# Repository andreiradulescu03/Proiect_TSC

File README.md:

# OpenBook – Proiect TSC 2025

Acest proiect reprezinta un prototip de eBook reader open-source, construit in jurul microcontrolerului ESP32-C6 si echipat cu afisaj E-Ink, baterie Li-Po, incarcare prin USB-C, slot microSD si senzori de mediu. Proiectul a inclus realizarea schemei electrice, a placii PCB, a modelului 3D complet si a fisierelor pentru fabricatie.

---

## Diagrama bloc

```mermaid
flowchart TB
  USB-C -->|5V| CHG["Battery Charger MCP73831"]
  CHG -->|Charging| BAT["LiPo Battery"]
  BAT --> LDO["3.3V LDO Regulator"]
  LDO -->|3.3V| ESP["ESP32-C6"]
  LDO -->|3.3V| EPD["E-Ink Display"]
  LDO -->|3.3V| SD["SD Card"]
  LDO -->|3.3V| BME["Sensor BME688"]
  LDO -->|3.3V| RTC["RTC DS3231"]
  LDO -->|3.3V| MAX["Battery Monitor MAX17048"]
  
  ESP -- SPI --> EPD
  ESP -- SPI --> SD
  ESP -- I2C --> BME
  ESP -- I2C --> RTC
  ESP -- I2C --> MAX
  ESP -- GPIO --> BTN["Buttons (3x)"]
```

---

## Functionalitate hardware

- **ESP32-C6** gestioneaza toate perifericele prin GPIO, SPI si I2C
- **Afisajul E-Ink** este controlat prin SPI si are semnale dedicate pentru RESET, DC si BUSY
- **Bateria Li-Po** este incarcata printr-un controler MCP73831 si monitorizata cu MAX17048
- **Senzorul BME688** masoara temperatura, umiditatea, presiunea si compusii volatili
- **Modulul RTC DS3231** mentine ora exacta si permite deep sleep eficient
- **Cardul microSD** este conectat la aceeasi magistrala SPI
- Toate componentele sunt montate pe layer-ul TOP si rutarea este realizata in 2 straturi

---

## Pinout ESP32-C6

| Componenta         | Pin ESP32-C6 | Interfata |
|--------------------|--------------|-----------|
| E-Ink BUSY         | IO3          | GPIO      |
| E-Ink DC           | IO5          | GPIO      |
| E-Ink RESET        | IO23         | GPIO      |
| E-Ink CS           | IO10         | SPI       |
| E-Ink MOSI         | IO7          | SPI       |
| E-Ink SCK          | IO6          | SPI       |
| SD Card CS         | IO4          | SPI       |
| SD Card MISO       | IO2          | SPI       |
| I2C SDA            | IO18         | I2C       |
| I2C SCL            | IO19         | I2C       |
| Butoane            | GPIO10/11/12 | GPIO      |

---

## Fisiere incluse

- `*.sch`, `*.brd` – schema electrica si design-ul PCB
- `Gerber/` – fisiere de productie
- `3D/` – modelul 3D al PCB-ului cu toate componentele atasate (baterie, ecran, carcasa)
- `BOM.csv` – lista de componente
- `README.md` – acest fisier

---

## Observatii

- Traseele de alimentare au latimea de 0.3mm, restul traseelor 0.15mm
- PCB-ul are grosimea de 1mm si contine planuri de masa pe ambele straturi
- Conectorii, ecranul si bateria au fost integrati in modelul 3D si testati pentru incadrare in carcasa
- Carcasa a fost importata si aliniata cu PCB-ul pentru randare
- Fisierele au fost verificate cu ERC si DRC

---

## Disclaimer subtil

Acest proiect a fost realizat cu atentie la detalii si cu efort considerabil, in contextul unor cerinte tehnice variate si din ce in ce mai ambitioase. Procesul de proiectare in Fusion 360 a oferit ocazii multiple de invatare, unele mai interesante decat altele. Daca anumite alegeri de design par neasteptate, ele reflecta acest parcurs complex.

---

## Bill of Materials

|   Qty | Value                                                                          | Device                                                                         | Package                                                | Parts                                                                                                   | Description                                                                                                                                                                                                                                                                                                                                                                                                                                                                                          |
|------:|:-------------------------------------------------------------------------------|:-------------------------------------------------------------------------------|:-------------------------------------------------------|:--------------------------------------------------------------------------------------------------------|:-----------------------------------------------------------------------------------------------------------------------------------------------------------------------------------------------------------------------------------------------------------------------------------------------------------------------------------------------------------------------------------------------------------------------------------------------------------------------------------------------------|
|     1 |                                                                                | ADAFRUIT_LEDCHIP-LED0603                                                       | ADAFRUIT_CHIP-LED0603                                  | CHG_LED                                                                                                 | LED                                                                                                                                                                                                                                                                                                                                                                                                                                                                                                  |
|     1 |                                                                                | SJ                                                                             | SJ                                                     | SJ1                                                                                                     | SMD solder JUMPER                                                                                                                                                                                                                                                                                                                                                                                                                                                                                    |
|     1 | 0.47                                                                           | ESP32_WROVER_EAGLE-LTSPICE_RR0402                                              | ESP32_WROVER_EAGLE-LTSPICE_R0402                       | R3                                                                                                      | RESISTOR, European symbol                                                                                                                                                                                                                                                                                                                                                                                                                                                                            |
|     1 | 100k                                                                           | ESP32_WROVER_EAGLE-LTSPICE_RR0402                                              | ESP32_WROVER_EAGLE-LTSPICE_R0402                       | R1_PWRUSB                                                                                               | RESISTOR, European symbol                                                                                                                                                                                                                                                                                                                                                                                                                                                                            |
|     7 | 100nF                                                                          | EAGLE-LTSPICE_CC0402                                                           | EAGLE-LTSPICE_C0402                                    | C1, C2, C4_USB, C6, C8, C10, C_DELAY                                                                    | CAPACITOR, European symbol                                                                                                                                                                                                                                                                                                                                                                                                                                                                           |
|     1 | 100uF                                                                          | EAGLE-LTSPICE_CC0402                                                           | EAGLE-LTSPICE_C0402                                    | C9                                                                                                      | CAPACITOR, European symbol                                                                                                                                                                                                                                                                                                                                                                                                                                                                           |
|     1 | 100uF                                                                          | RCL_CPOL-EUCT3528                                                              | RCL_CT3528                                             | C3                                                                                                      | POLARIZED CAPACITOR, European symbol                                                                                                                                                                                                                                                                                                                                                                                                                                                                 |
|    16 | 10k                                                                            | ESP32_WROVER_EAGLE-LTSPICE_RR0402                                              | ESP32_WROVER_EAGLE-LTSPICE_R0402                       | R1, R1_PINH, R1_PINH1, R2_PINH, R2_PINH1, R4, R5, R6, R7, R8, R9, R10, R_BOOT, R_CHANGE, R_CL1, R_RESET | RESISTOR, European symbol                                                                                                                                                                                                                                                                                                                                                                                                                                                                            |
|     1 | 10uF                                                                           | EAGLE-LTSPICE_CC0402                                                           | EAGLE-LTSPICE_C0402                                    | C7                                                                                                      | CAPACITOR, European symbol                                                                                                                                                                                                                                                                                                                                                                                                                                                                           |
|     1 | 112A-TAAR-R03_ATTEND                                                           | 112A-TAAR-R03_ATTEND                                                           | 112ATAARR03ATTEND                                      | J4                                                                                                      | Micro SD Card Socket, Push-Push Type, Top Mount, SMT, H=1.83mm, 10u                                                                                                                                                                                                                                                                                                                                                                                                                                  |
|     1 | 15                                                                             | ESP32_WROVER_EAGLE-LTSPICE_RR0402                                              | ESP32_WROVER_EAGLE-LTSPICE_R0402                       | R_CAPACITOR                                                                                             | RESISTOR, European symbol                                                                                                                                                                                                                                                                                                                                                                                                                                                                            |
|     1 | 1uF                                                                            | EAGLE-LTSPICE_CC0402                                                           | EAGLE-LTSPICE_C0402                                    | C5                                                                                                      | CAPACITOR, European symbol                                                                                                                                                                                                                                                                                                                                                                                                                                                                           |
|    10 | 1uF/50V                                                                        | EAGLE-LTSPICE_CC0402                                                           | EAGLE-LTSPICE_C0402                                    | EPD_C1, EPD_C2, EPD_C5, EPD_C6, EPD_C7, EPD_C8, EPD_C9, EPD_C10, EPD_C11, EPD_C12                       | CAPACITOR, European symbol                                                                                                                                                                                                                                                                                                                                                                                                                                                                           |
|     1 | 2.2                                                                            | ESP32_WROVER_EAGLE-LTSPICE_RR0402                                              | ESP32_WROVER_EAGLE-LTSPICE_R0402                       | R2                                                                                                      | RESISTOR, European symbol                                                                                                                                                                                                                                                                                                                                                                                                                                                                            |
|     1 | 200                                                                            | ESP32_WROVER_EAGLE-LTSPICE_RR0402                                              | ESP32_WROVER_EAGLE-LTSPICE_R0402                       | R1_BAT                                                                                                  | RESISTOR, European symbol                                                                                                                                                                                                                                                                                                                                                                                                                                                                            |
|     2 | 20V/4.2A/52mO/1.4W                                                             | ESP32_WROVER_SPARKFUN-DISCRETESEMI_MOSFET_PCH-DMG2305UX-7                      | ESP32_WROVER_SPARKFUN-DISCRETESEMI_SOT23-3             | Q1, Q2                                                                                                  | P-channel MOSFETs                                                                                                                                                                                                                                                                                                                                                                                                                                                                                    |
|     1 | 2k                                                                             | ESP32_WROVER_EAGLE-LTSPICE_RR0402                                              | ESP32_WROVER_EAGLE-LTSPICE_R0402                       | R2_BAT                                                                                                  | RESISTOR, European symbol                                                                                                                                                                                                                                                                                                                                                                                                                                                                            |
|     5 | 4.7uF                                                                          | EAGLE-LTSPICE_CC0402                                                           | EAGLE-LTSPICE_C0402                                    | C1_BAT, C1_BAT1, C1_BAT2, C2_BAT, C5_USB                                                                | CAPACITOR, European symbol                                                                                                                                                                                                                                                                                                                                                                                                                                                                           |
|     1 | 4.7uF/25V                                                                      | EAGLE-LTSPICE_CC0402                                                           | EAGLE-LTSPICE_C0402                                    | C4                                                                                                      | CAPACITOR, European symbol                                                                                                                                                                                                                                                                                                                                                                                                                                                                           |
|     2 | 5k1                                                                            | ESP32_WROVER_EAGLE-LTSPICE_RR0402                                              | ESP32_WROVER_EAGLE-LTSPICE_R0402                       | R2-USB, R2-USB1                                                                                         | RESISTOR, European symbol                                                                                                                                                                                                                                                                                                                                                                                                                                                                            |
|     1 | 68uH                                                                           | 744043680IND_4828-WE-TPC_WRE                                                   | IND_4828-WE-TPC_WRE                                    | L1                                                                                                      |                                                                                                                                                                                                                                                                                                                                                                                                                                                                                                      |
|     1 | BD5229G-TR                                                                     | BD5229G-TR                                                                     | SOT95P280X125-5N                                       | IC1                                                                                                     | Voltage Detector with Adjustable Delay Time: CMOS processes are utilized to develop high precision, low current consumption CMOS reset ICs that allow arbitrary setting of the delay time. The extensive lineup includes both Nch Open Drain and CMOS output types in a wide range of detection voltages (from 2.3V to 6.0V, in 0.1V steps), enabling selection of the ideal solution based on customer requirements. In addition, the entire series is of course both lead-free and RoHS-compliant. |
|     3 | BUTTON_CUSYOMV1                                                                | BUTTON_CUSYOMV1                                                                | MYBUTTON                                               | BOOT_BUTTON, CHANGE_BUTTON, RESET_BUTTON                                                                |                                                                                                                                                                                                                                                                                                                                                                                                                                                                                                      |
|     1 | CPH3225A                                                                       | CPH3225A                                                                       | CAPCP3225X100N                                         | C10_SUPERCAP                                                                                            | Cap 0.011F 3.3V 1210 Flat Check availability                                                                                                                                                                                                                                                                                                                                                                                                                                                         |
|     1 | DS3231SN#                                                                      | DS3231SN#                                                                      | SOIC127P1032X265-16N                                   | U3                                                                                                      | Real Time Clock Serial 16-Pin SOIC W T/R     Check availability                                                                                                                                                                                                                                                                                                                                                                                                                                      |
|     1 | ESP32-C6-WROOM-1-N8                                                            | ESP32-C6-WROOM-1-N8                                                            | XCVR_ESP32-C6-WROOM-1-N8                               | U2                                                                                                      | Check availability                                                                                                                                                                                                                                                                                                                                                                                                                                                                                   |
|     1 | ESP32C6_VARISTORCN1812                                                         | ESP32C6_VARISTORCN1812                                                         | ESP32C6_VARISTOR_CT/CN1812                             | PFMF.050.1                                                                                              | VARISTOR                                                                                                                                                                                                                                                                                                                                                                                                                                                                                             |
|     2 | ESP32_WROVER_AVX---SD0805S020S1R0_AVX_SD0805S020S1R0_0_0AVX_SD0805S020S1R0_0_0 | ESP32_WROVER_AVX---SD0805S020S1R0_AVX_SD0805S020S1R0_0_0AVX_SD0805S020S1R0_0_0 | ESP32_WROVER_AVX---SD0805S020S1R0_AVX_SD0805S020S1R0_0 | D2, D7                                                                                                  | Schottky Barrier Rectifier Diode                                                                                                                                                                                                                                                                                                                                                                                                                                                                     |
|     1 | ESP32_WROVER_BME680_BME680                                                     | ESP32_WROVER_BME680_BME680                                                     | ESP32_WROVER_BME680_PSON80P300X300X100-8N              | SENSOR2                                                                                                 | Integrated Environmental Unit                                                                                                                                                                                                                                                                                                                                                                                                                                                                        |
|     1 | ESP32_WROVER_SPARKFUN-IC-POWER_MCP73831                                        | ESP32_WROVER_SPARKFUN-IC-POWER_MCP73831                                        | ESP32_WROVER_SPARKFUN-IC-POWER_SOT23-5                 | MCP73831                                                                                                | MCP73831T Li-Ion, Li-Pol Controller                                                                                                                                                                                                                                                                                                                                                                                                                                                                  |
|     1 | FH34SRJ-24S-0.5SH_99_                                                          | FH34SRJ-24S-0.5SH_99_                                                          | FH34SRJ24S05SH99                                       | J1                                                                                                      | (0.50mm) Surface Mount, Right Angle                                                                                                                                                                                                                                                                                                                                                                                                                                                                  |
|     1 | MAX17048G+T10                                                                  | MAX17048G+T10                                                                  | SON50P200X200X80-9N                                    | U4                                                                                                      | Check availability                                                                                                                                                                                                                                                                                                                                                                                                                                                                                   |
|     3 | MBR0530                                                                        | MBR0530                                                                        | SOD3716X135N                                           | D3, D4, D5                                                                                              | ON SEMICONDUCTOR - MBR0530 - DIODE, SCHOTTKY, 0.5A, 30V, SOD-123                                                                                                                                                                                                                                                                                                                                                                                                                                     |
|     6 | PGB1010603MR                                                                   | PGB1010603MR                                                                   | DIOC1608X36N                                           | D6, D8, D9, D10, D11, D12                                                                               | Check availability                                                                                                                                                                                                                                                                                                                                                                                                                                                                                   |
|     1 | QWIIC_RIGHT_ANGLE                                                              | QWIIC_CONNECTORJS-1MM                                                          | JST04_1MM_RA                                           | J3                                                                                                      | SparkFun I2C Standard Qwiic Connector                                                                                                                                                                                                                                                                                                                                                                                                                                                                |
|     1 | SAMACSYS_PARTS_USB4110-GF-A                                                    | SAMACSYS_PARTS_USB4110-GF-A                                                    | SAMACSYS_PARTS_USB4110GFA                              | J2                                                                                                      | CONN USB 2.0 TYPE-C R/A SMT                                                                                                                                                                                                                                                                                                                                                                                                                                                                          |
|     1 | SI1308EDL-T1-GE3                                                               | SI1308EDL-T1-GE3                                                               | SOT65P210X110-3N                                       | Q3                                                                                                      | MOSFET N-Ch 30V 1.5A TrenchFET SC70 Vishay Si1308EDL-T1-GE3 N-channel MOSFET Transistor, 1.5 A, 30 V, 3-Pin SC-70                                                                                                                                                                                                                                                                                                                                                                                    |
|    17 | TPTP20R                                                                        | TPTP20R                                                                        | TP20R                                                  | TP1, TP2, TP3, TP4, TP5, TP6, TP7, TP8, TP9, TP10, TP11, TP12, TP13, TP14, TP15, TP16, TP17             | Test pad                                                                                                                                                                                                                                                                                                                                                                                                                                                                                             |
|     1 | USBLC6-2SC6Y                                                                   | USBLC6-2SC6Y                                                                   | SOT95P280X145-6N                                       | D1                                                                                                      | Low Cap. ESD Protection Auto SOT-23-6 STMicroelectronics USBLC6-2SC6Y, Dual Uni-Directional TVS Diode Array, 6-Pin SOT-23                                                                                                                                                                                                                                                                                                                                                                            |
|     1 | W25Q512JVEIQ                                                                   | W25Q512JVEIQ                                                                   | SON127P600X800X80-9N                                   | U1                                                                                                      | Check availability                                                                                                                                                                                                                                                                                                                                                                                                                                                                                   |
|     1 | XC6220A331MR-G                                                                 | XC6220A331MR-G                                                                 | SOT95P280X120-5N                                       | IC4                                                                                                     | LDO Voltage Regulators                                                                                                                                                                                                                                                                                                                                                                                                                                                                               |

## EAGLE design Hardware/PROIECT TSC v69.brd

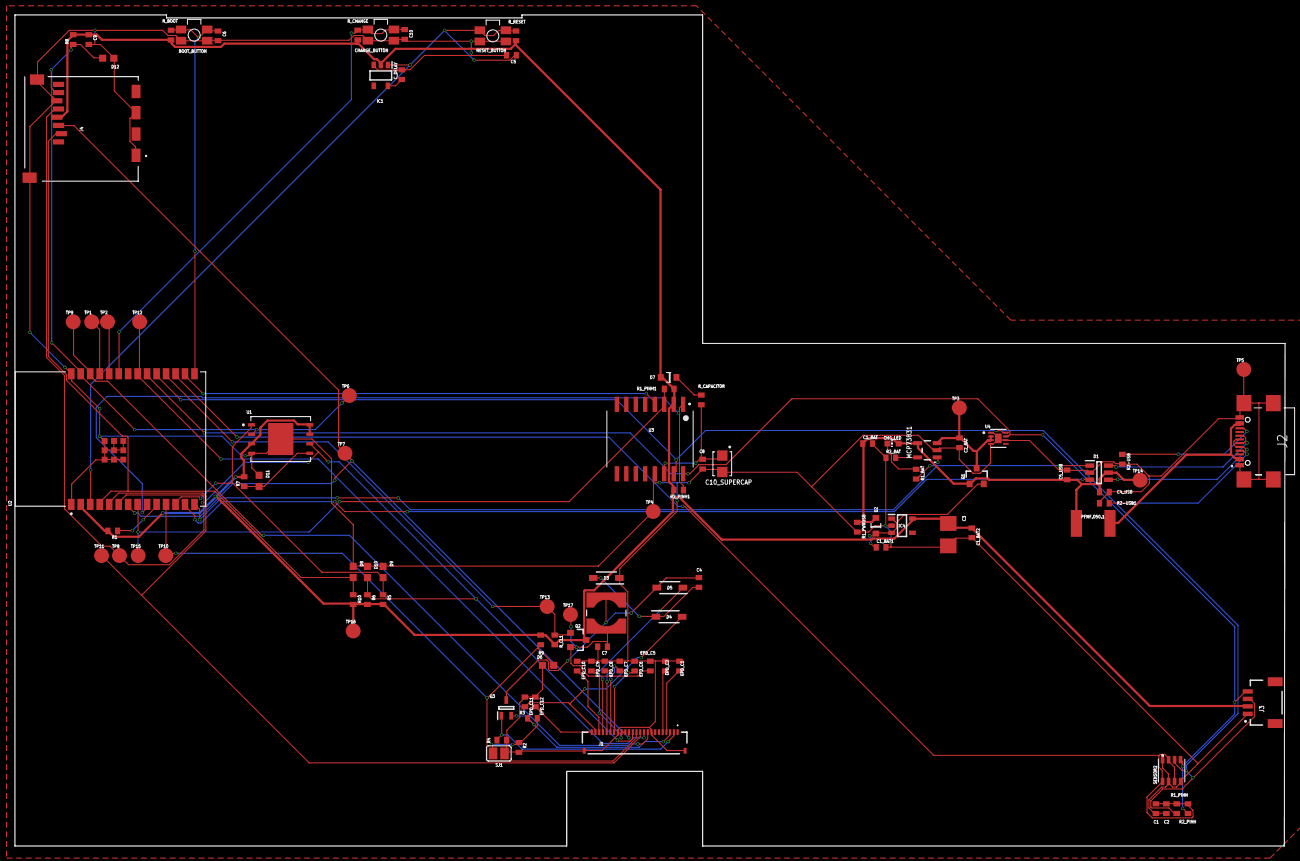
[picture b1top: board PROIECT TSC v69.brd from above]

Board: 2 copper layers, 170.1 x 111.3 mm, 103 parts (0 on the bottom side), 55 nets.

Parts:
BOOT_BUTTON: BUTTON_CUSYOMV1; MYBUTTON
C1, C2, C4_USB, C6, C8, C10: 100nF; EAGLE-LTSPICE_C0402
C1_BAT, C1_BAT1, C1_BAT2, C2_BAT, C5_USB: 4.7uF; EAGLE-LTSPICE_C0402
C3: 100uF; RCL_CT3528
C4: 4.7uF/25V; EAGLE-LTSPICE_C0402
C5: 1uF; EAGLE-LTSPICE_C0402
C7: 10uF; EAGLE-LTSPICE_C0402
C9: 100uF; EAGLE-LTSPICE_C0402
C10_SUPERCAP: CPH3225A; CAPCP3225X100N
CHANGE_BUTTON: BUTTON_CUSYOMV1; MYBUTTON
CHG_LED: ADAFRUIT_CHIP-LED0603
C_DELAY: 100nF; EAGLE-LTSPICE_C0402
D1: USBLC6-2SC6Y; SOT95P280X145-6N
D2, D7: ESP32_WROVER_AVX---SD0805S020S1R0_AVX_SD0805S020S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; ESP32_WROVER_AVX---SD0805S020S1R0_AVX_SD0805S020S1R0_0
D3, D4, D5: MBR0530; SOD3716X135N
D6, D8, D9, D10, D11, D12: PGB1010603MR; DIOC1608X36N
EPD_C1, EPD_C2, EPD_C5, EPD_C6, EPD_C7, EPD_C8, EPD_C9, EPD_C10, EPD_C11, EPD_C12: 1uF/50V; EAGLE-LTSPICE_C0402
IC1: BD5229G-TR; SOT95P280X125-5N
IC4: XC6220A331MR-G; SOT95P280X120-5N
J1: FH34SRJ-24S-0.5SH_99_; FH34SRJ24S05SH99
J2: SAMACSYS_PARTS_USB4110-GF-A; SAMACSYS_PARTS_USB4110GFA
J3: QWIIC_RIGHT_ANGLE; JST04_1MM_RA
J4: 112A-TAAR-R03_ATTEND; 112ATAARR03ATTEND
L1: 68uH; IND_4828-WE-TPC_WRE
MCP73831: ESP32_WROVER_SPARKFUN-IC-POWER_MCP73831; ESP32_WROVER_SPARKFUN-IC-POWER_SOT23-5
PFMF.050.1: ESP32C6_VARISTORCN1812; ESP32C6_VARISTOR_CT/CN1812
Q1, Q2: 20V/4.2A/52mΩ/1.4W; ESP32_WROVER_SPARKFUN-DISCRETESEMI_SOT23-3
Q3: SI1308EDL-T1-GE3; SOT65P210X110-3N
R1, R1_PINH, R1_PINH1, R2_PINH, R2_PINH1, R4, R5, R6, R7, R8, R9, R10: 10k; ESP32_WROVER_EAGLE-LTSPICE_R0402
R1_BAT: 200; ESP32_WROVER_EAGLE-LTSPICE_R0402
R1_PWRUSB: 100k; ESP32_WROVER_EAGLE-LTSPICE_R0402
R2: 2.2; ESP32_WROVER_EAGLE-LTSPICE_R0402
R2-USB, R2-USB1: 5k1; ESP32_WROVER_EAGLE-LTSPICE_R0402
R2_BAT: 2k; ESP32_WROVER_EAGLE-LTSPICE_R0402
R3: 0.47; ESP32_WROVER_EAGLE-LTSPICE_R0402
RESET_BUTTON: BUTTON_CUSYOMV1; MYBUTTON
R_BOOT: 10k; ESP32_WROVER_EAGLE-LTSPICE_R0402
R_CAPACITOR: 15; ESP32_WROVER_EAGLE-LTSPICE_R0402
R_CHANGE: 10k; ESP32_WROVER_EAGLE-LTSPICE_R0402
R_CL1: 10k; ESP32_WROVER_EAGLE-LTSPICE_R0402
R_RESET: 10k; ESP32_WROVER_EAGLE-LTSPICE_R0402
SENSOR2: ESP32_WROVER_BME680_BME680; ESP32_WROVER_BME680_PSON80P300X300X100-8N
SJ1: SJ
TP1, TP2, TP3, TP4, TP5, TP6, TP7, TP8, TP9, TP10, TP11, TP12, TP13, TP14, TP15, TP16, TP17: TPTP20R; TP20R
U1: W25Q512JVEIQ; SON127P600X800X80-9N
U2: ESP32-C6-WROOM-1-N8; XCVR_ESP32-C6-WROOM-1-N8
U3: DS3231SN#; SOIC127P1032X265-16N
U4: MAX17048G+T10; SON50P200X200X80-9N

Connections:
3V3: C1_BAT2.1, C3.+, C9.1, D7.2, IC1.2, IC4.5, J3.2, J4.P4, Q2.3, R1.2, R1_PINH1.1, R2_PINH1.1, R5.2, R6.2, R7.2, R8.2, R9.2, R10.2, R_BOOT.2, R_CHANGE.2, R_CL1.2, R_RESET.2, TP16.TP, U1.3, U1.7, U1.8, U2.2, U3.2
32KHZ: R2_PINH1.2, U2.9, U3.1
DN: D1.4, J2.A7, J2.B7
DP: D1.6, J2.A6, J2.B6
EPD_3V3: C7.1, EPD_C5.2, J1.15, J1.16, L1.2, Q2.2, TP17.TP
EPD_3V3_C: Q2.1, R_CL1.1, TP13.TP, U2.18
EPD_BUSY: J1.9, TP9.TP, U2.26
EPD_CS: D6.2, J1.12, R9.1, TP10.TP, U2.11
EPD_DC: J1.11, TP11.TP, U2.5
EPD_RST: J1.10, TP12.TP, U2.21
FLASH_CS: D9.2, R5.1, U1.1, U2.12
GDR: J1.2, Q3.1, R4.2
GND: BOOT_BUTTON.1, BOOT_BUTTON.2, C1.2, C1_BAT.2, C1_BAT1.2, C1_BAT2.2, C2.2, C2_BAT.2, C3.-, C4_USB.2, C5.2, C5_USB.2, C6.2, C7.2, C8.1, C9.2, C10.2, C10_SUPERCAP.2, CHANGE_BUTTON.1, CHANGE_BUTTON.2, C_DELAY.2, D1.2, D3.1, D6.1, D8.1, D9.1, D10.1, D11.1, D12.1, EPD_C1.1, EPD_C2.1, EPD_C5.1, EPD_C6.1, EPD_C7.1, EPD_C8.1, EPD_C9.1, EPD_C10.1, EPD_C11.1, EPD_C12.1, IC1.3, IC4.2, J1.8, J1.17, J1.MP1, J1.MP2, J2.A1, J2.A12, J2.B1, J2.B12, J2.MP1, J2.MP2, J2.MP3, J2.MP4, J3.1, J4.G1, J4.G2, J4.G3, J4.G4, J4.P6, MCP73831.2, R1_PWRUSB.1, R2.1, R2-USB.2, R2-USB1.1, R2_BAT.1, R4.1, RESET_BUTTON.1, RESET_BUTTON.2, SENSOR2.1, SENSOR2.5, SENSOR2.7, SJ1.1, TP4.TP, TP5.TP, U1.4, U1.9, U2.1, U2.28, U2.29_1, U2.29_2, U2.29_3, U2.29_4, U2.29_5, U2.29_6, U2.29_7, U2.29_8, U2.29_9, U3.13, U4.1, U4.4, U4.6, U4.9
GPIO8: R1.1, U2.10
I2C_PW: C1.1, C2.1, R1_PINH.2, R2_PINH.2, SENSOR2.2, SENSOR2.6, SENSOR2.8, U2.17
INT_RTC: R1_PINH1.2, TP15.TP, U2.8, U3.3
IO/BOOT: BOOT_BUTTON.3, BOOT_BUTTON.4, C6.1, R_BOOT.1, U2.15
IO/CHANGE: C10.1, CHANGE_BUTTON.3, CHANGE_BUTTON.4, R_CHANGE.1, U2.23
MISO: D12.2, J4.P7, R8.1, TP6.TP, U1.2, U2.27
MOSI: D11.2, J1.14, J4.P3, R7.1, TP7.TP, U1.5, U2.7
unnamed: C4.1, D3.2, D4.1
unnamed: J2.A5, R2-USB1.2
unnamed: MCP73831.1, R1_BAT.2
unnamed: C1_BAT1.1, D2.1, IC4.1, IC4.3, Q1.2
unnamed: CHG_LED.C, R1_BAT.1
unnamed: MCP73831.5, R2_BAT.2
unnamed: EPD_C12.2, J1.24
unnamed: EPD_C8.2, J1.20
unnamed: EPD_C10.2, J1.22
unnamed: EPD_C7.2, J1.19
unnamed: EPD_C6.2, J1.18
unnamed: J2.B5, R2-USB.1
unnamed: EPD_C2.2, J1.5
unnamed: EPD_C1.2, J1.4
unnamed: C_DELAY.1, IC1.5
unnamed: D7.1, R_CAPACITOR.2
PREVGH: D5.1, EPD_C9.2, J1.21
PREVGL: D4.2, EPD_C11.2, J1.23
RESE: J1.3, Q3.2, R3.2
RESE': R2.2, R3.1, SJ1.2
RESET: C5.1, IC1.1, RESET_BUTTON.3, RESET_BUTTON.4, R_RESET.1, U2.3
RTC_RST: U2.16, U3.4
RX: TP2.TP, U2.24
SCK: D10.2, J1.13, J4.P5, R6.1, TP8.TP, U1.6, U2.6
SCL: J3.4, R2_PINH.1, SENSOR2.4, U2.20, U3.16, U4.7
SDA: J3.3, R1_PINH.1, SENSOR2.3, U2.19, U3.15, U4.8
SRC: C4.2, D5.2, L1.1, Q3.3
SS_SD: D8.2, J4.P2, R10.1, U2.4
TX: TP1.TP, U2.25
USB_D+: D1.1, U2.14
USB_D-: D1.3, U2.13
VBAT: C2_BAT.1, MCP73831.3, Q1.3, TP3.TP, U4.2, U4.3
VBUS: C1_BAT.1, C4_USB.1, C5_USB.1, CHG_LED.A, D1.5, D2.2, MCP73831.4, PFMF.050.1.2, Q1.1, R1_PWRUSB.2, TP14.TP
VRTC: C8.2, C10_SUPERCAP.1, R_CAPACITOR.1, U3.14
VUSB: J2.A4, J2.A9, J2.B4, J2.B9, PFMF.050.1.1

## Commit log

2025-04-06 Primul commit - adaugare proiect TSC
2025-04-15 Upload proiect local complet

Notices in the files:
parts and their libraries:
COPYRIGHT: Copyright (C) 2024 Ultra Librarian. All rights reserved.
